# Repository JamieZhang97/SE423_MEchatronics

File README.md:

# SE423_Mechatronics

This course is learning to program a TI MSP430 microcontroller. In the final project, I design eletronics and mechanism to build a segbot. Also I need to program the segbot to keep it balance and move.

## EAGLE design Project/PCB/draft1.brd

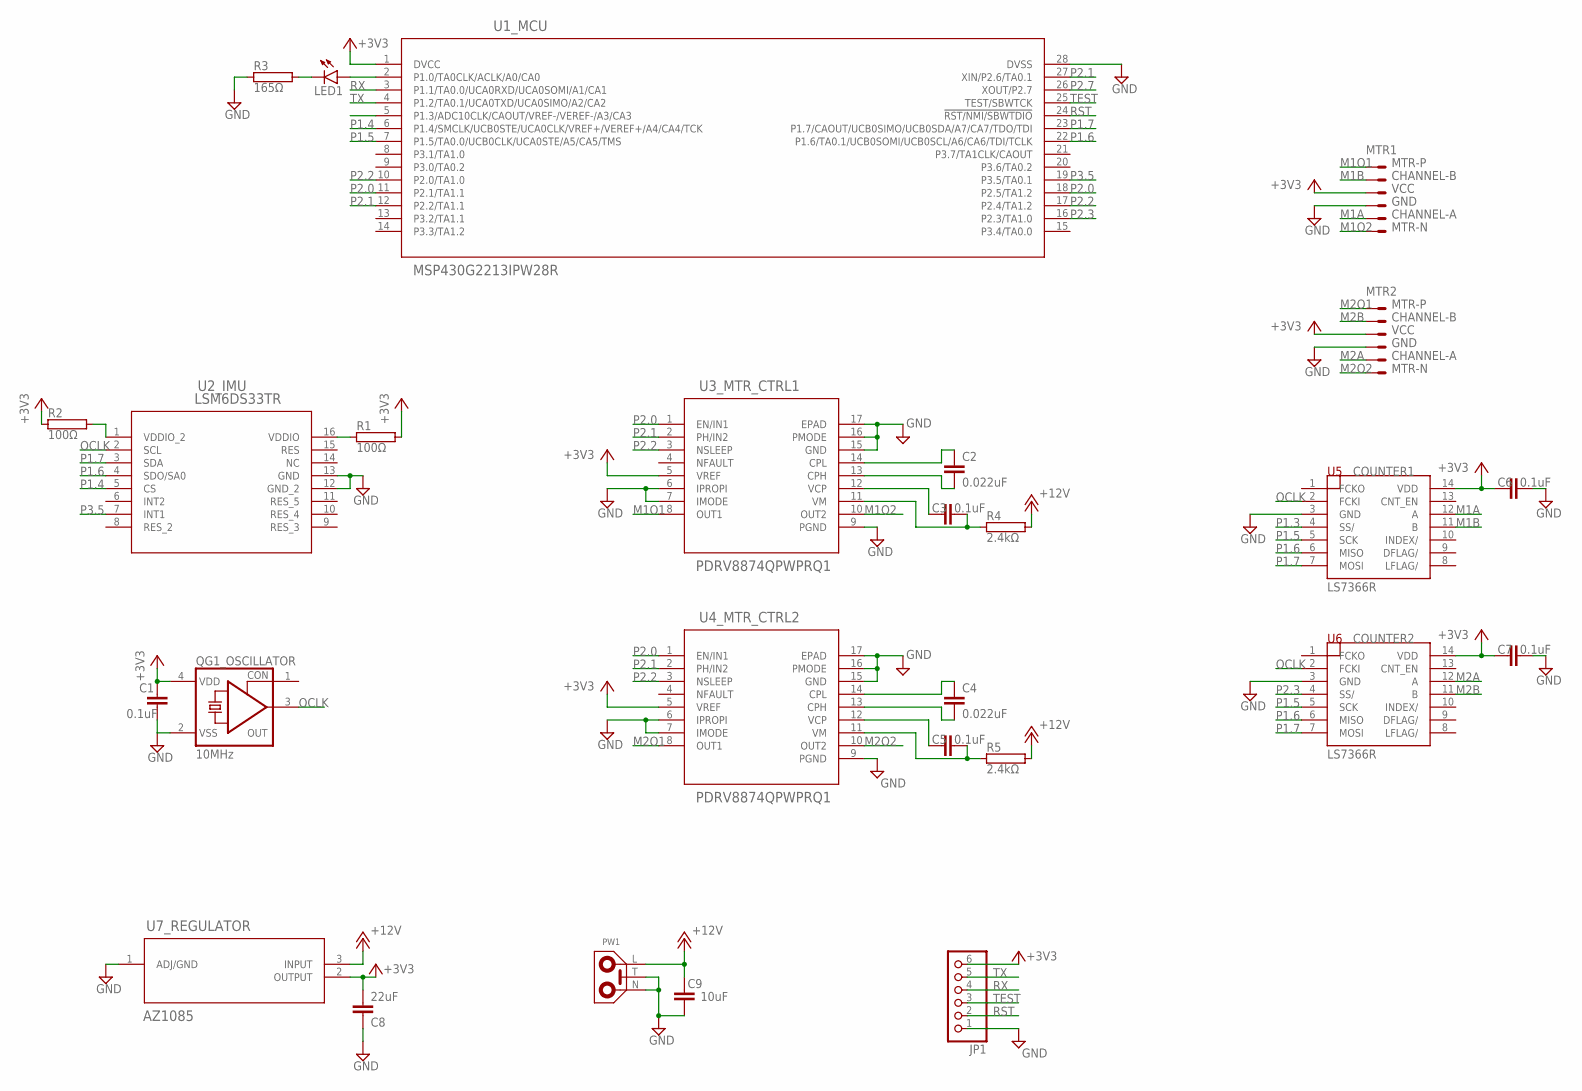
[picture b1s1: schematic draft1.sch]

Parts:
C1, C3, C5, C6, C7: 0.1uF; C2.5-2
C2, C4: 0.022uF; C2.5-2
C8: 22uF; C2.5-2
C9: 10uF; C2.5-2
JP1: PINHD-1X6; 1X06
LED1: LED5MM
MTR1, MTR2: JST-XH-06-PIN-ROUND-PAD; JST-XH-06-PACKAGE-ROUND-PAD
PW1: POWER-PM
QG1_OSCILLATOR: 10MHz; 1100S
R1, R2: 100Ω; AC01
R3: 165Ω; AC01
R4, R5: 2.4kΩ; AC01
U1_MCU: MSP430G2213IPW28R; PW28
U2_IMU: LSM6DS33TR; LGA-16L_3X3
U3_MTR_CTRL1, U4_MTR_CTRL2: PDRV8874QPWPRQ1; PWP16
U5, U6: LS7366R; SO14
U7_REGULATOR: AZ1085; TO-263_DIO

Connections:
+3V3: C1.1, C6.1, C7.1, C8.2, JP1.6, MTR1.3, MTR2.3, QG1_OSCILLATOR.4 (VDD), R1.2, R2.1, U1_MCU.1 (DVCC), U3_MTR_CTRL1.5 (VREF), U4_MTR_CTRL2.5 (VREF), U5.14 (VDD), U6.14 (VDD), U7_REGULATOR.2 (OUTPUT)
+12V: C9.1, PW1.L (1), R4.2, R5.2, U7_REGULATOR.3 (INPUT)
GND: C1.2, C6.2, C7.2, C8.1, C9.2, JP1.1, MTR1.4, MTR2.4, PW1.N (2), PW1.T, QG1_OSCILLATOR.2 (VSS), R3.1, U1_MCU.28 (DVSS), U2_IMU.12 (GND_2), U2_IMU.13 (GND), U3_MTR_CTRL1.6 (IPROPI), U3_MTR_CTRL1.7 (IMODE), U3_MTR_CTRL1.9 (PGND), U3_MTR_CTRL1.15 (GND), U3_MTR_CTRL1.16 (PMODE), U3_MTR_CTRL1.17 (EPAD), U4_MTR_CTRL2.6 (IPROPI), U4_MTR_CTRL2.7 (IMODE), U4_MTR_CTRL2.9 (PGND), U4_MTR_CTRL2.15 (GND), U4_MTR_CTRL2.16 (PMODE), U4_MTR_CTRL2.17 (EPAD), U5.3 (GND), U6.3 (GND), U7_REGULATOR.1 (ADJ/GND)
M1A: MTR1.5, U5.12 (A)
M1B: MTR1.2, U5.11 (B)
M1O1: MTR1.1, U3_MTR_CTRL1.8 (OUT1)
M1O2: MTR1.6, U3_MTR_CTRL1.10 (OUT2)
M2A: MTR2.5, U6.12 (A)
M2B: MTR2.2, U6.11 (B)
M2O1: MTR2.1, U4_MTR_CTRL2.8 (OUT1)
M2O2: MTR2.6, U4_MTR_CTRL2.10 (OUT2)
unnamed: LED1.A, U1_MCU.2 (P1.0/TA0CLK/ACLK/A0/CA0)
unnamed: R2.2, U2_IMU.1 (VDDIO_2)
unnamed: R1.1, U2_IMU.16 (VDDIO)
unnamed: LED1.K (C), R3.2
unnamed: C2.1, U3_MTR_CTRL1.14 (CPL)
unnamed: C2.2, U3_MTR_CTRL1.13 (CPH)
unnamed: C3.1, U3_MTR_CTRL1.12 (VCP)
unnamed: C4.1, U4_MTR_CTRL2.14 (CPL)
unnamed: C3.2, R4.1, U3_MTR_CTRL1.11 (VM)
unnamed: C4.2, U4_MTR_CTRL2.13 (CPH)
unnamed: C5.1, U4_MTR_CTRL2.12 (VCP)
unnamed: C5.2, R5.1, U4_MTR_CTRL2.11 (VM)
OCLK: QG1_OSCILLATOR.3 (OUT), U2_IMU.2 (SCL), U5.2 (FCKI), U6.2 (FCKI)
P1.3: U5.4 (SS/)
P1.4: U1_MCU.6 (P1.4/SMCLK/UCB0STE/UCA0CLK/VREF+/VEREF+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), U2_IMU.5 (CS)
P1.5: U1_MCU.7 (P1.5/TA0.0/UCB0CLK/UCA0STE/A5/CA5/TMS), U5.5 (SCK), U6.5 (SCK)
P1.6: U1_MCU.22 (P1.6/TA0.1/UCB0SOMI/UCB0SCL/A6/CA6/TDI/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), U2_IMU.4 (SDO/SA0), U5.6 (MISO), U6.6 (MISO)
P1.7: U1_MCU.23 (P1.7/CAOUT/UCB0SIMO/UCB0SDA/A7/CA7/TDO/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), U2_IMU.3 (SDA), U5.7 (MOSI), U6.7 (MOSI)
P2.0: U1_MCU.11 (P2.1/TA1.1), U1_MCU.18 (P2.5/TA1.2), U3_MTR_CTRL1.1 (EN/IN1), U4_MTR_CTRL2.1 (EN/IN1)
P2.1: U1_MCU.12 (P2.2/TA1.1), U1_MCU.27 (XIN/P2.6/TA0.1), U3_MTR_CTRL1.2 (PH/IN2), U4_MTR_CTRL2.2 (PH/IN2)
P2.2: U1_MCU.10 (P2.0/TA1.0), U1_MCU.17 (P2.4/TA1.2), U3_MTR_CTRL1.3 (NSLEEP), U4_MTR_CTRL2.3 (NSLEEP)
P2.3: U1_MCU.16 (P2.3/TA1.0), U6.4 (SS/)
P2.7: U1_MCU.26 (XOUT/P2.7)
P3.5: U1_MCU.19 (P3.5/TA0.1), U2_IMU.7 (INT1)
RST: JP1.2, U1_MCU.24 (!RST/NMI/SBWTDIO)
RX: JP1.4, U1_MCU.3 (P1.1/TA0.0/UCA0RXD/UCA0SOMI/A1/CA1)
TEST: JP1.3, U1_MCU.25 (TEST/SBWTCK)
TX: JP1.5, U1_MCU.4 (P1.2/TA0.1/UCA0TXD/UCA0SIMO/A2/CA2)

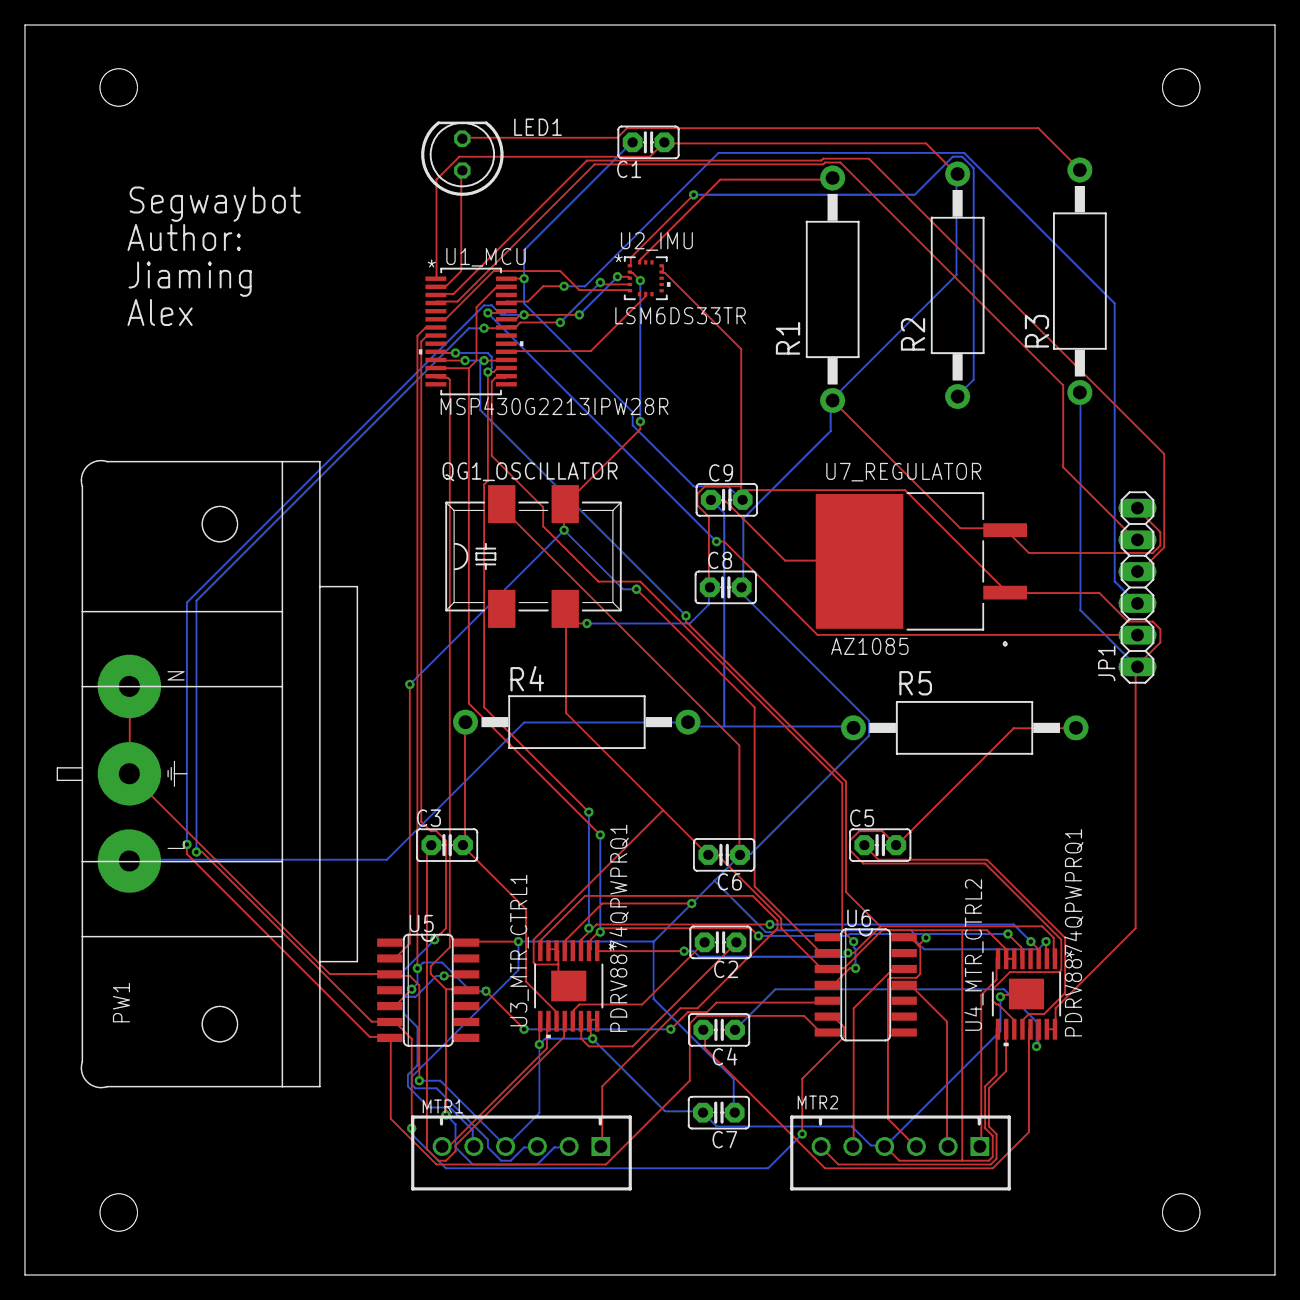
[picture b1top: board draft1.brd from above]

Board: 2 copper layers, 100.0 x 100.0 mm, 27 parts (0 on the bottom side), 37 nets.

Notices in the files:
parts and their libraries:
COPYRIGHT: Copyright (C) 2018 Accelerated Designs. All rights reserved
